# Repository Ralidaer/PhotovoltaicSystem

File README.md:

# PhotovoltaicSystem

WORK IN PROGRESS

Engineering work entitled "A solar system following the sun"
This is a repository for files associated with my engineering work. This repository contain arduino program, photos and word document.
<p>
Demonstration of action (timelapse):

https://user-images.githubusercontent.com/92920833/138950048-f2738cb1-5066-4342-91d9-b7f5de5a17e9.mp4

Subsequent stages of construction:
<p>

<p>

<p>

<p>

<p>

<p>
  
<p>

<p>

<p>

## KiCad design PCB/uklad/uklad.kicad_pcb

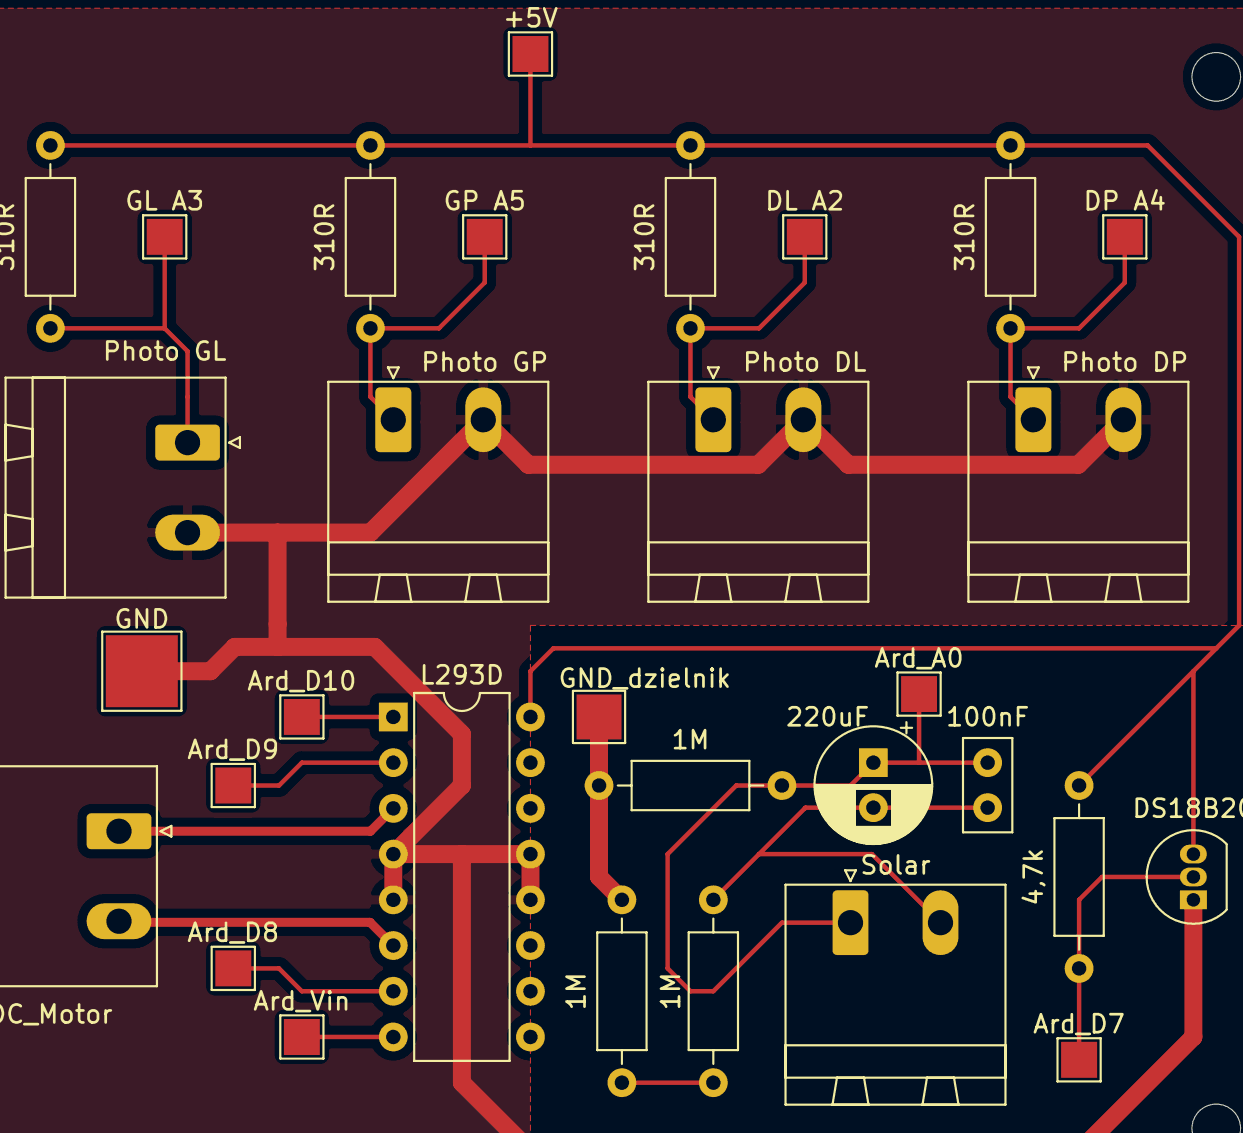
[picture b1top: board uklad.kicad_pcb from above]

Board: 2 copper layers, 31 parts (0 on the bottom side), 12 nets.

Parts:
1M, 1M#2, 1M#3: 1M; R_Axial_DIN0207_L6.3mm_D2.5mm_P10.16mm_Horizontal
4,7k: 4,7k; R_Axial_DIN0207_L6.3mm_D2.5mm_P10.16mm_Horizontal
100nF: 100nF; C_Disc_D5.0mm_W2.5mm_P2.50mm
220uF: 220uF; CP_Radial_D6.3mm_P2.50mm
310R, 310R#2, 310R#3, 310R#4: 310R; R_Axial_DIN0207_L6.3mm_D2.5mm_P10.16mm_Horizontal
+5V: TestPoint_Pad_2.0x2.0mm
Ard_A0: TestPoint_Pad_2.0x2.0mm
Ard_D7, Ard_D8, Ard_D9, Ard_D10: TestPoint_Pad_2.0x2.0mm
Ard_Vin: TestPoint_Pad_2.0x2.0mm
DC_Motor: Motor_DC; PhoenixContact_MSTBA_2,5_2-G_1x02_P5.00mm_Horizontal
DL A2: TestPoint_Pad_2.0x2.0mm
DP A4: TestPoint_Pad_2.0x2.0mm
DS18B20: DS18B20; TO-92_Inline
GL A3: TestPoint_Pad_2.0x2.0mm
GND: TestPoint_Pad_4.0x4.0mm
GND_dzielnik: TestPoint_Pad_2.5x2.5mm
GP A5: TestPoint_Pad_2.0x2.0mm
L293D: L293D; DIP-16_W7.62mm
Photo DL: 50-100k; PhoenixContact_MSTBA_2,5_2-G_1x02_P5.00mm_Horizontal
Photo DP: 50-100k; PhoenixContact_MSTBA_2,5_2-G_1x02_P5.00mm_Horizontal
Photo GL: 50-100k; PhoenixContact_MSTBA_2,5_2-G_1x02_P5.00mm_Horizontal
Photo GP: 50-100k; PhoenixContact_MSTBA_2,5_2-G_1x02_P5.00mm_Horizontal
Solar: 9V; PhoenixContact_MSTBA_2,5_2-G_1x02_P5.00mm_Horizontal

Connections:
+5V: 4,7k.1, 310R.1, 310R#2.1, 310R#3.1, 310R#4.1, DS18B20.3, L293D.16
GND: 1M#2.1, 1M#3.2, DS18B20.1, L293D.4, L293D.5, L293D.12, L293D.13, Photo DL.2, Photo DP.2, Photo GL.2, Photo GP.2
unnamed: 310R#4.2, Photo GL.1
unnamed: 310R#3.2, Photo GP.1
unnamed: 310R#2.2, Photo DL.1
unnamed: 310R.2, Photo DP.1
unnamed: 1M#3.1, 100nF.1, 220uF.1, Solar.1
unnamed: 4,7k.2, DS18B20.2
unnamed: 1M.2, 100nF.2, 220uF.2, Solar.2
unnamed: DC_Motor.1, L293D.3
unnamed: DC_Motor.2, L293D.6
unnamed: 1M.1, 1M#2.2

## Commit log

2021-10-26 add videos, photos, docx file and PCB project
2021-10-26 change readme
2021-10-26 change readme again
2021-10-27 end of 3 chapter
2021-11-06 Removing docx
2021-12-18 removing files
2021-12-18 new files
